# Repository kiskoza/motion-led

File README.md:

# ESP8266 Motion Led

Turn on / off a led strip with a motion detector.

## Getting Started

### Prerequisites

You need to install `python` to use PlatformIO and `nodejs` + `yarn` to run Webpacker. Best way to do is install via asdf version manager.

```
asdf plugin add python
asdf plugin add nodejs
asdf plugin add yarn
asdf install
```

We need to install required packages

```
pip install -r requirements.txt
yarn install
```

And configure the environment variables

```
cp .env.example .env
nano .env
```

### Running

Then we could run a dev-server for the web

```
yarn run dev
```

... or build the whole project

```
yarn run build
```

## Running the tests

Currently there's no tests :(

Luckily we've got some code-style checkers:

```
yarn run lint
```

## Board

You can build the board based on the included KiCad project

## Deployment

Plug in the ESP module and:

```
yarn run deploy
```

## Built With

* [asdf-vm](https://asdf-vm.com/) - For easy install
* [KiCad EDA](https://kicad.org/) - For the hardware layout
* [PlatformIO](https://platformio.org/) - For the ESP module
* [Webpack](https://webpack.js.org/) - For the web interface

## Contributing

Please read [CONTRIBUTING.md](CONTRIBUTING.md) for details on our code of conduct, and the process for submitting pull requests to us.

## Versioning

We use [SemVer](http://semver.org/) for versioning. For the versions available, see the [tags on this repository](https://github.com/kiskoza/motion-led/tags).

## License

This project is licensed under the MIT License - see the [LICENSE.md](LICENSE.md) file for details

## Acknowledgments

* Hat tip to anyone whose code was used
* Inspiration
* etc

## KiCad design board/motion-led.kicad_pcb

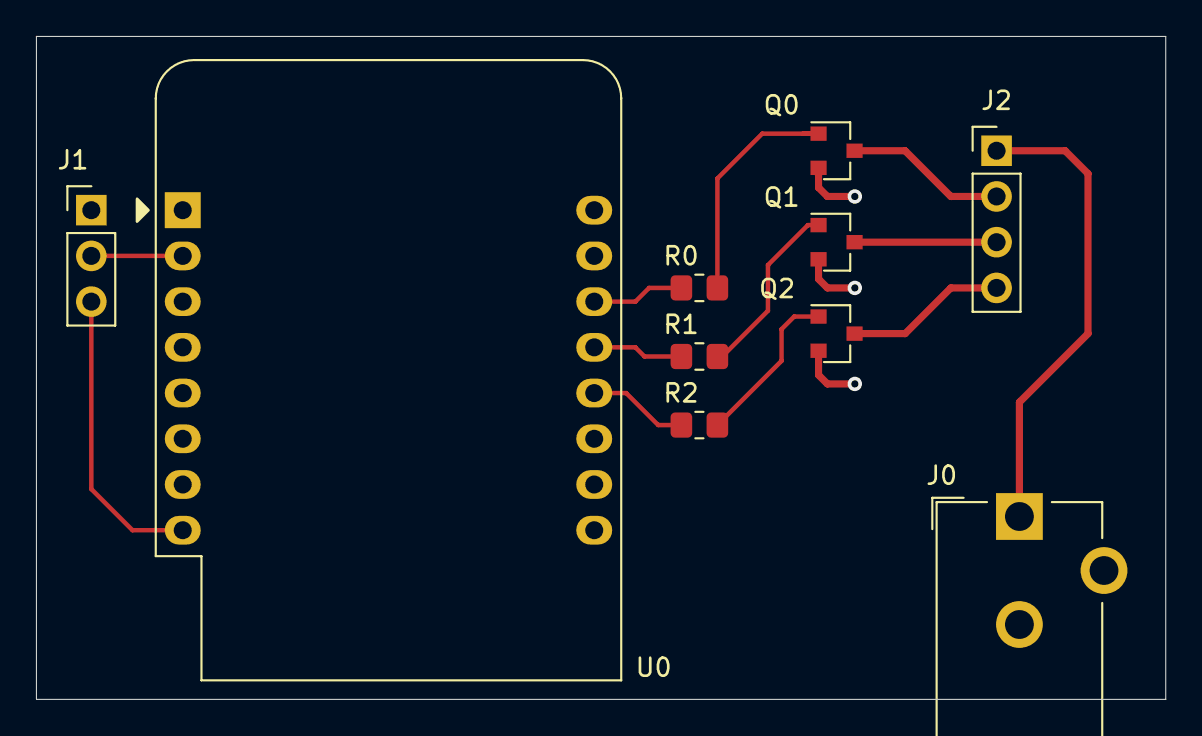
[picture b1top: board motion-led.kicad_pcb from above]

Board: 2 copper layers, 62.7 x 36.8 mm, 10 parts (0 on the bottom side), 13 nets.

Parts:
J0: Barrel_Jack; BarrelJack_CUI_PJ-102AH_Horizontal
J1: AM312; PinHeader_1x03_P2.54mm_Vertical
J2: LED PINs; PinHeader_1x04_P2.54mm_Vertical
Q0, Q1, Q2: 2N7002; SOT-23
R0, R1, R2: 1; R_0805_2012Metric_Pad1.20x1.40mm_HandSolder
U0: WeMos_D1_mini; WEMOS_D1_mini_light

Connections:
GND: J0.2, J1.1, Q0.2, Q1.2, Q2.2, U0.10
unnamed: J0.1, J2.1
unnamed: J1.2, U0.2
unnamed: J1.3, U0.8
unnamed: J2.2, Q0.3
unnamed: J2.3, Q1.3
unnamed: J2.4, Q2.3
unnamed: Q0.1, R0.1
unnamed: Q1.1, R1.1
unnamed: Q2.1, R2.1
unnamed: R0.2, U0.14
unnamed: R1.2, U0.13
unnamed: R2.2, U0.12

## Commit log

2019-11-18 Small changes to sample
2019-11-18 Change project name from template
2019-11-18 Read PIR sensor with analog input, turn on builtin led on motion
2019-11-20 Move web related codes to web.h & web.cpp
2020-03-15 Bump acorn from 6.3.0 to 6.4.1
    Bumps [acorn](https://github.com/acornjs/acorn) from 6.3.0 to 6.4.1.
    - [Release notes](https://github.com/acornjs/acorn/releases)
    - [Commits](https://github.com/acornjs/acorn/compare/6.3.0...6.4.1)
2020-06-07 Bump websocket-extensions from 0.1.3 to 0.1.4
    Bumps [websocket-extensions](https://github.com/faye/websocket-extensions-node) from 0.1.3 to 0.1.4.
    - [Release notes](https://github.com/faye/websocket-extensions-node/releases)
    - [Changelog](https://github.com/faye/websocket-extensions-node/blob/master/CHANGELOG.md)
    - [Commits](https://github.com/faye/websocket-extensions-node/compare/0.1.3...0.1.4)
2020-07-18 Bump lodash from 4.17.15 to 4.17.19
    Bumps [lodash](https://github.com/lodash/lodash) from 4.17.15 to 4.17.19.
    - [Release notes](https://github.com/lodash/lodash/releases)
    - [Commits](https://github.com/lodash/lodash/compare/4.17.15...4.17.19)
2020-08-01 Bump elliptic from 6.5.1 to 6.5.3
    Bumps [elliptic](https://github.com/indutny/elliptic) from 6.5.1 to 6.5.3.
    - [Release notes](https://github.com/indutny/elliptic/releases)
    - [Commits](https://github.com/indutny/elliptic/compare/v6.5.1...v6.5.3)
2020-09-10 Bump http-proxy from 1.18.0 to 1.18.1
    Bumps [http-proxy](https://github.com/http-party/node-http-proxy) from 1.18.0 to 1.18.1.
    - [Release notes](https://github.com/http-party/node-http-proxy/releases)
    - [Changelog](https://github.com/http-party/node-http-proxy/blob/master/CHANGELOG.md)
    - [Commits](https://github.com/http-party/node-http-proxy/compare/1.18.0...1.18.1)
2020-10-04 Add board schematic
2020-10-04 Update board schema
2020-10-04 Assign footprints and check electrical rules
2020-10-04 fix for PWR_FLAGs
2020-10-04 Ignore net files - they could be regenerated anytime
2020-10-04 Move led's 12V to the first pin
2021-02-10 PCB layout for the board
2021-02-10 Finalize PCB
2021-02-10 Bump ini from 1.3.5 to 1.3.8
    Bumps [ini](https://github.com/isaacs/ini) from 1.3.5 to 1.3.8.
    - [Release notes](https://github.com/isaacs/ini/releases)
    - [Commits](https://github.com/isaacs/ini/compare/v1.3.5...v1.3.8)
2021-03-09 Bump elliptic from 6.5.3 to 6.5.4
    Bumps [elliptic](https://github.com/indutny/elliptic) from 6.5.3 to 6.5.4.
    - [Release notes](https://github.com/indutny/elliptic/releases)
    - [Commits](https://github.com/indutny/elliptic/compare/v6.5.3...v6.5.4)
2021-04-30 Bump ssri from 6.0.1 to 6.0.2
    Bumps [ssri](https://github.com/npm/ssri) from 6.0.1 to 6.0.2.
    - [Release notes](https://github.com/npm/ssri/releases)
    - [Changelog](https://github.com/npm/ssri/blob/v6.0.2/CHANGELOG.md)
    - [Commits](https://github.com/npm/ssri/compare/v6.0.1...v6.0.2)
2021-05-08 Bump url-parse from 1.4.7 to 1.5.1
    Bumps [url-parse](https://github.com/unshiftio/url-parse) from 1.4.7 to 1.5.1.
    - [Release notes](https://github.com/unshiftio/url-parse/releases)
    - [Commits](https://github.com/unshiftio/url-parse/compare/1.4.7...1.5.1)
2021-05-10 Bump lodash from 4.17.19 to 4.17.21
    Bumps [lodash](https://github.com/lodash/lodash) from 4.17.19 to 4.17.21.
    - [Release notes](https://github.com/lodash/lodash/releases)
    - [Commits](https://github.com/lodash/lodash/compare/4.17.19...4.17.21)
2021-05-28 Bump dns-packet from 1.3.1 to 1.3.4
    Bumps [dns-packet](https://github.com/mafintosh/dns-packet) from 1.3.1 to 1.3.4.
    - [Release notes](https://github.com/mafintosh/dns-packet/releases)
    - [Changelog](https://github.com/mafintosh/dns-packet/blob/master/CHANGELOG.md)
    - [Commits](https://github.com/mafintosh/dns-packet/compare/v1.3.1...v1.3.4)
2021-06-05 Bump ws from 6.2.1 to 6.2.2
    Bumps [ws](https://github.com/websockets/ws) from 6.2.1 to 6.2.2.
    - [Release notes](https://github.com/websockets/ws/releases)
    - [Commits](https://github.com/websockets/ws/commits)
    ---
    updated-dependencies:
    - dependency-name: ws
2021-07-24 Changed placing for a more easy-to-read schematic Fixed gate resisor values to match microcontroller output current limitations Added discharge resistor to gate drive
2021-07-24 Dummy commit, same as above
2021-07-24 Added schottky diode for reverse polarity protection Added frames and names to different parts of the schematic
2021-07-24 Added parts list to the PCB design
2021-07-24 Fixed Gate resistors to maintain 33mA consumption on GPIOs
2021-07-24 Fixed transistor in parts_list.md
2021-07-24 Fixed transistor types to mach the specifications
2021-07-26 Fixed power supply, now 5V is connected to the ESP and the motion sensor Fixed badly placed flags
2021-07-26 Fixed parts_list.md to mach current PCB design
2021-08-02 Fix voltage values on schematic
2021-08-02 Add dataseet for AM312 PIR sensor
2021-08-02 Update part list and schematics
2021-08-04 Bump tar from 4.4.13 to 4.4.15
    Bumps [tar](https://github.com/npm/node-tar) from 4.4.13 to 4.4.15.
    - [Release notes](https://github.com/npm/node-tar/releases)
    - [Changelog](https://github.com/npm/node-tar/blob/main/CHANGELOG.md)
    - [Commits](https://github.com/npm/node-tar/compare/v4.4.13...v4.4.15)
    ---
    updated-dependencies:
2021-09-02 Bump tar from 4.4.13 to 4.4.19
    Bumps [tar](https://github.com/npm/node-tar) from 4.4.13 to 4.4.19.
    - [Release notes](https://github.com/npm/node-tar/releases)
    - [Changelog](https://github.com/npm/node-tar/blob/main/CHANGELOG.md)
    - [Commits](https://github.com/npm/node-tar/compare/v4.4.13...v4.4.19)
    ---
    updated-dependencies:
2021-09-17 Added efficient, switching regulator based power supply
2021-09-17 Added 12V flag to the new pwr supply
2021-09-20 Added low pass filter to ESP power pin
2021-10-06 Bump url-parse from 1.4.7 to 1.5.3
    Bumps [url-parse](https://github.com/unshiftio/url-parse) from 1.4.7 to 1.5.3.
    - [Release notes](https://github.com/unshiftio/url-parse/releases)
    - [Commits](https://github.com/unshiftio/url-parse/compare/1.4.7...1.5.3)
    ---
    updated-dependencies:
    - dependency-name: url-parse
2021-11-08 Update README.md
    https://forum.kicad.info/t/warning-avoid-all-links-to-kicad-pcb-org-use-kicad-org/31521
2022-01-14 Bump follow-redirects from 1.13.0 to 1.14.7
    Bumps [follow-redirects](https://github.com/follow-redirects/follow-redirects) from 1.13.0 to 1.14.7.
    - [Release notes](https://github.com/follow-redirects/follow-redirects/releases)
    - [Commits](https://github.com/follow-redirects/follow-redirects/compare/v1.13.0...v1.14.7)
    ---
    updated-dependencies:
    - dependency-name: follow-redirects
2022-02-12 Bump ajv from 6.10.2 to 6.12.6
    Bumps [ajv](https://github.com/ajv-validator/ajv) from 6.10.2 to 6.12.6.
    - [Release notes](https://github.com/ajv-validator/ajv/releases)
    - [Commits](https://github.com/ajv-validator/ajv/compare/v6.10.2...v6.12.6)
    ---
    updated-dependencies:
    - dependency-name: ajv
2022-02-13 Bump follow-redirects from 1.13.0 to 1.14.8
    Bumps [follow-redirects](https://github.com/follow-redirects/follow-redirects) from 1.13.0 to 1.14.8.
    - [Release notes](https://github.com/follow-redirects/follow-redirects/releases)
    - [Commits](https://github.com/follow-redirects/follow-redirects/compare/v1.13.0...v1.14.8)
    ---
    updated-dependencies:
    - dependency-name: follow-redirects
2022-02-18 Bump url-parse from 1.4.7 to 1.5.7
    Bumps [url-parse](https://github.com/unshiftio/url-parse) from 1.4.7 to 1.5.7.
    - [Release notes](https://github.com/unshiftio/url-parse/releases)
    - [Commits](https://github.com/unshiftio/url-parse/compare/1.4.7...1.5.7)
    ---
    updated-dependencies:
    - dependency-name: url-parse
2022-02-26 Bump url-parse from 1.4.7 to 1.5.10
    Bumps [url-parse](https://github.com/unshiftio/url-parse) from 1.4.7 to 1.5.10.
    - [Release notes](https://github.com/unshiftio/url-parse/releases)
    - [Commits](https://github.com/unshiftio/url-parse/compare/1.4.7...1.5.10)
    ---
    updated-dependencies:
    - dependency-name: url-parse
2022-04-29 Bump async from 2.6.3 to 2.6.4
    Bumps [async](https://github.com/caolan/async) from 2.6.3 to 2.6.4.
    - [Release notes](https://github.com/caolan/async/releases)
    - [Changelog](https://github.com/caolan/async/blob/v2.6.4/CHANGELOG.md)
    - [Commits](https://github.com/caolan/async/compare/v2.6.3...v2.6.4)
    ---
    updated-dependencies:
2022-06-01 Bump eventsource from 1.0.7 to 1.1.1
    Bumps [eventsource](https://github.com/EventSource/eventsource) from 1.0.7 to 1.1.1.
    - [Release notes](https://github.com/EventSource/eventsource/releases)
    - [Changelog](https://github.com/EventSource/eventsource/blob/master/HISTORY.md)
    - [Commits](https://github.com/EventSource/eventsource/compare/v1.0.7...v1.1.1)
    ---
    updated-dependencies:
2022-07-20 Bump terser from 4.4.0 to 4.8.1
    Bumps [terser](https://github.com/terser/terser) from 4.4.0 to 4.8.1.
    - [Release notes](https://github.com/terser/terser/releases)
    - [Changelog](https://github.com/terser/terser/blob/master/CHANGELOG.md)
    - [Commits](https://github.com/terser/terser/commits)
    ---
    updated-dependencies:
2022-12-04 Bump decode-uri-component from 0.2.0 to 0.2.2
    Bumps [decode-uri-component](https://github.com/SamVerschueren/decode-uri-component) from 0.2.0 to 0.2.2.
    - [Release notes](https://github.com/SamVerschueren/decode-uri-component/releases)
    - [Commits](https://github.com/SamVerschueren/decode-uri-component/compare/v0.2.0...v0.2.2)
    ---
    updated-dependencies:
    - dependency-name: decode-uri-component
2022-12-11 Bump express from 4.17.1 to 4.18.2
    Bumps [express](https://github.com/expressjs/express) from 4.17.1 to 4.18.2.
    - [Release notes](https://github.com/expressjs/express/releases)
    - [Changelog](https://github.com/expressjs/express/blob/master/History.md)
    - [Commits](https://github.com/expressjs/express/compare/4.17.1...4.18.2)
    ---
    updated-dependencies:
